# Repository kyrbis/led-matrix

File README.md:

# led-matrix
led matrix board
:)!!

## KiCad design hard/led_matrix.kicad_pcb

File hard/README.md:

# LED Matrix hardware
via KiCad (https://kicad.org/), tuned for order on JLCPCB (https://jlcpcb.com/).  
All capacitors X7R or better.

_PCB Preview_

## KiCad Readme
### Libraries (*.lib)
Additional fields/attributes as in following example:

| Name | Value |
| ----:|:----- |
| DigiKey | IRLML0030TRPBFCT-ND |
| Mouser | 942-IRLML0030TRPBF |
| LCSC | C67272 |
| MF | Infineon Technologies |
| MPN | IRLML0030TRPBF |
| Description | MOSFET N-CH 30V 5.3A SOT23 |

### Footprints (*.pretty)
_See https://kicad.org/libraries/klc/_

Use naming scheme `TYPE_MF_PART`  
Example: `LED_LiteOn_LTST-S270TBKT.kicad_mod`

### 3D (*.step)
Use same naming scheme as for footprints in dedicated 3D folder. In order to see 3D packages, setup `${LED_MATRIX_3D}` as path for your own folder.   
Example: `./3D/LED_LiteOn_LTST-S270TBKT.step`

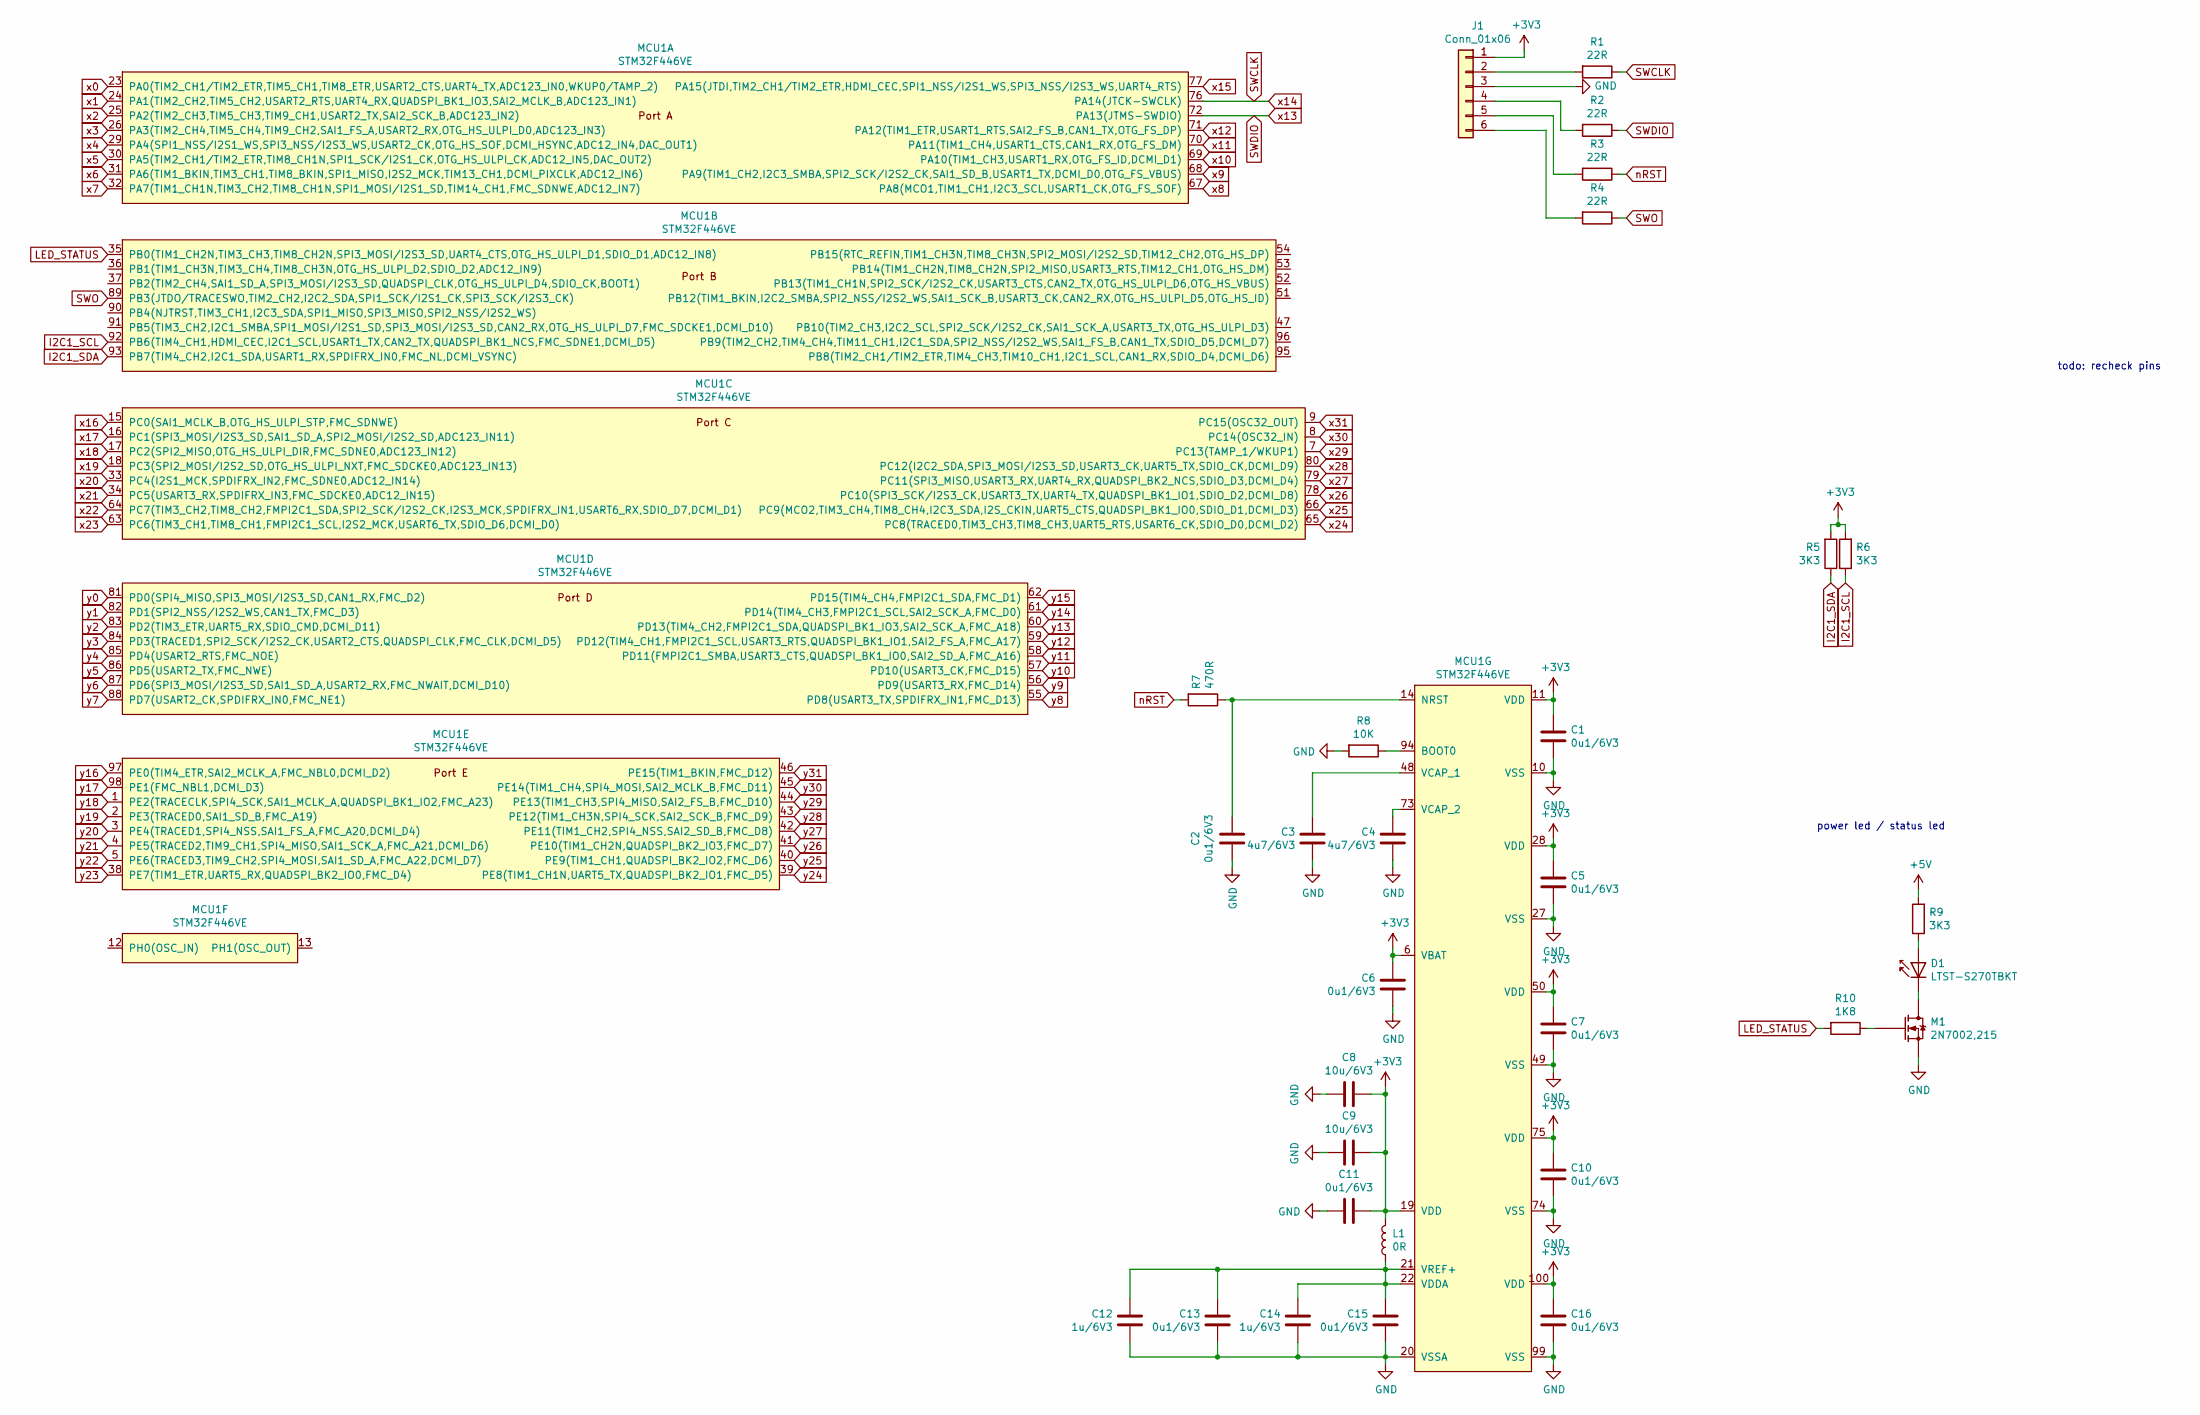
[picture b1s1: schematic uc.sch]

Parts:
C1, C2, C5, C6, C7, C10, C11, C13, C15, C16: 0u1/6V3; C_0402_1005Metric
C3, C4: 4u7/6V3; C_0805_2012Metric
C8, C9: 10u/6V3; C_0805_2012Metric
C12, C14: 1u/6V3; C_0805_2012Metric
D1: LTST-S270TBKT; LED_LiteOn_LTST-S270TBKT; Mouser_Part_Number 859-LTST-S270TBKT; DigiKey_Part_Number LTST-S270TBKT-5A-ND
J1: Conn_01x06; PinHeader_1x06_P2.54mm_Vertical
L1: 0R; R_1206_3216Metric
M1: 2N7002,215; SOT-23; MPN 2N7002,215; JLCPCB_Part_Number C65189
MCU1: STM32F446VE; MPN STM32F446VET6; JLCPCB_Part_Number C91929
R1, R2, R3, R4: 22R; R_0402_1005Metric
R5, R6, R9: 3K3; R_0402_1005Metric
R7: 470R; R_0402_1005Metric
R8: 10K; R_0402_1005Metric
R10: 1K8; R_0402_1005Metric

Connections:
+3V3: C1.1, C5.1, C6.2, C7.1, C8.2, C9.2, C10.1, C11.2, C16.1, J1.1, L1.1, MCU1.6 (VBAT), MCU1.11 (VDD), MCU1.19 (VDD), MCU1.28 (VDD), MCU1.50 (VDD), MCU1.75 (VDD), MCU1.100 (VDD), R5.2, R6.2; also elsewhere on the board
+5V: R9.2; also elsewhere on the board
GND: C1.2, C2.1, C3.1, C4.1, C5.2, C6.1, C7.2, C8.1, C9.1, C10.2, C11.1, C12.1, C13.1, C14.1, C15.1, C16.2, J1.3, M1.2 (S), MCU1.10 (VSS), MCU1.20 (VSSA), MCU1.27 (VSS), MCU1.49 (VSS), MCU1.74 (VSS), MCU1.99 (VSS), R8.2; also elsewhere on the board
I2C1_SCL: MCU1.92 (PB6(TIM4_CH1,HDMI_CEC,I2C1_SCL,USART1_T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), R6.1; also elsewhere on the board
I2C1_SDA: MCU1.93 (PB7(TIM4_CH2,I2C1_SDA,USART1_RX,SPDIFRX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), R5.1; also elsewhere on the board
LED_STATUS: MCU1.35 (PB0(TIM1_CH2N,TIM3_CH3,TIM8_CH2N,SPI3_M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), R10.2
unnamed: C2.2, MCU1.14 (NRST), R7.1
unnamed: C3.2, MCU1.48 (VCAP_1)
unnamed: C4.2, MCU1.73 (VCAP_2)
unnamed: C12.2, C13.2, C14.2, C15.2, L1.2, MCU1.21 (VREF+), MCU1.22 (VDDA)
unnamed: D1.A, R9.1
unnamed: D1.C, M1.3 (D)
unnamed: J1.2, R1.2
unnamed: J1.4, R2.2
unnamed: J1.5, R3.2
unnamed: J1.6, R4.2
unnamed: M1.1 (G), R10.1
unnamed: MCU1.94 (BOOT0), R8.1
SWCLK: MCU1.76 (PA14(JTCK-SWCLK)), R1.1; also elsewhere on the board
SWDIO: MCU1.72 (PA13(JTMS-SWDIO)), R2.1; also elsewhere on the board
SWO: MCU1.89 (PB3(JTDO/TRACESWO,TIM2_CH2,I2C2_SDA,SPI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), R4.1
nRST: R3.1, R7.2
x0: MCU1.23 (PA0(TIM2_CH1/TIM2_ETR,TIM5_CH1,TIM8_ETR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); also elsewhere on the board
x1: MCU1.24 (PA1(TIM2_CH2,TIM5_CH2,USART2_RTS,UART4_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); also elsewhere on the board
x2: MCU1.25 (PA2(TIM2_CH3,TIM5_CH3,TIM9_CH1,USART2_T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); also elsewhere on the board
x3: MCU1.26 (PA3(TIM2_CH4,TIM5_CH4,TIM9_CH2,SAI1_FS_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); also elsewhere on the board
x4: MCU1.29 (PA4(SPI1_NSS/I2S1_WS,SPI3_NSS/I2S3_WS,U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); also elsewhere on the board
x5: MCU1.30 (PA5(TIM2_CH1/TIM2_ETR,TIM8_CH1N,SPI1_SC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); also elsewhere on the board
x6: MCU1.31 (PA6(TIM1_BKIN,TIM3_CH1,TIM8_BKIN,SPI1_M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); also elsewhere on the board
x7: MCU1.32 (PA7(TIM1_CH1N,TIM3_CH2,TIM8_CH1N,SPI1_M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); also elsewhere on the board
x8: MCU1.67 (PA8(MCO1,TIM1_CH1,I2C3_SCL,USART1_CK,OT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); also elsewhere on the board
x9: MCU1.68 (PA9(TIM1_CH2,I2C3_SMBA,SPI2_SCK/I2S2_CK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); also elsewhere on the board
x10: MCU1.69 (PA10(TIM1_CH3,USART1_RX,OTG_FS_ID,DCMI_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); also elsewhere on the board
x11: MCU1.70 (PA11(TIM1_CH4,USART1_CTS,CAN1_RX,OTG_FS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); also elsewhere on the board
x12: MCU1.71 (PA12(TIM1_ETR,USART1_RTS,SAI2_FS_B,CAN1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); also elsewhere on the board
x15: MCU1.77 (PA15(JTDI,TIM2_CH1/TIM2_ETR,HDMI_CEC,SP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); also elsewhere on the board
x16: MCU1.15 (PC0(SAI1_MCLK_B,OTG_HS_ULPI_STP,FMC_SDN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); also elsewhere on the board
x17: MCU1.16 (PC1(SPI3_MOSI/I2S3_SD,SAI1_SD_A,SPI2_MO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); also elsewhere on the board
x18: MCU1.17 (PC2(SPI2_MISO,OTG_HS_ULPI_DIR,FMC_SDNE0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); also elsewhere on the board
x19: MCU1.18 (PC3(SPI2_MOSI/I2S2_SD,OTG_HS_ULPI_NXT,F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); also elsewhere on the board
x20: MCU1.33 (PC4(I2S1_MCK,SPDIFRX_IN2,FMC_SDNE0,ADC1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); also elsewhere on the board
x21: MCU1.34 (PC5(USART3_RX,SPDIFRX_IN3,FMC_SDCKE0,AD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); also elsewhere on the board
x22: MCU1.64 (PC7(TIM3_CH2,TIM8_CH2,FMPI2C1_SDA,SPI2_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); also elsewhere on the board
x23: MCU1.63 (PC6(TIM3_CH1,TIM8_CH1,FMPI2C1_SCL,I2S2_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); also elsewhere on the board
x24: MCU1.65 (PC8(TRACED0,TIM3_CH3,TIM8_CH3,UART5_RTS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); also elsewhere on the board
x25: MCU1.66 (PC9(MCO2,TIM3_CH4,TIM8_CH4,I2C3_SDA,I2S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); also elsewhere on the board
x26: MCU1.78 (PC10(SPI3_SCK/I2S3_CK,USART3_TX,UART4_T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); also elsewhere on the board
x27: MCU1.79 (PC11(SPI3_MISO,USART3_RX,UART4_RX,QUADS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); also elsewhere on the board
x28: MCU1.80 (PC12(I2C2_SDA,SPI3_MOSI/I2S3_SD,USART3_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); also elsewhere on the board
x29: MCU1.7 (PC13(TAMP_1/WKUP1)); also elsewhere on the board
x30: MCU1.8 (PC14(OSC32_IN)); also elsewhere on the board
x31: MCU1.9 (PC15(OSC32_OUT)); also elsewhere on the board
y0: MCU1.81 (PD0(SPI4_MISO,SPI3_MOSI/I2S3_SD,CAN1_RX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); also elsewhere on the board
y1: MCU1.82 (PD1(SPI2_NSS/I2S2_WS,CAN1_TX,FMC_D3)); also elsewhere on the board
y2: MCU1.83 (PD2(TIM3_ETR,UART5_RX,SDIO_CMD,DCMI_D11)); also elsewhere on the board
y3: MCU1.84 (PD3(TRACED1,SPI2_SCK/I2S2_CK,USART2_CTS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); also elsewhere on the board
y4: MCU1.85 (PD4(USART2_RTS,FMC_NOE)); also elsewhere on the board
y5: MCU1.86 (PD5(USART2_TX,FMC_NWE)); also elsewhere on the board
y6: MCU1.87 (PD6(SPI3_MOSI/I2S3_SD,SAI1_SD_A,USART2_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); also elsewhere on the board
y7: MCU1.88 (PD7(USART2_CK,SPDIFRX_IN0,FMC_NE1)); also elsewhere on the board
y8: MCU1.55 (PD8(USART3_TX,SPDIFRX_IN1,FMC_D13)); also elsewhere on the board
y9: MCU1.56 (PD9(USART3_RX,FMC_D14)); also elsewhere on the board
y10: MCU1.57 (PD10(USART3_CK,FMC_D15)); also elsewhere on the board
y11: MCU1.58 (PD11(FMPI2C1_SMBA,USART3_CTS,QUADSPI_BK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); also elsewhere on the board
y12: MCU1.59 (PD12(TIM4_CH1,FMPI2C1_SCL,USART3_RTS,QU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); also elsewhere on the board
y13: MCU1.60 (PD13(TIM4_CH2,FMPI2C1_SDA,QUADSPI_BK1_I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); also elsewhere on the board
y14: MCU1.61 (PD14(TIM4_CH3,FMPI2C1_SCL,SAI2_SCK_A,FM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); also elsewhere on the board
y15: MCU1.62 (PD15(TIM4_CH4,FMPI2C1_SDA,FMC_D1)); also elsewhere on the board
y16: MCU1.97 (PE0(TIM4_ETR,SAI2_MCLK_A,FMC_NBL0,DCMI_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); also elsewhere on the board
y17: MCU1.98 (PE1(FMC_NBL1,DCMI_D3)); also elsewhere on the board
y18: MCU1.1 (PE2(TRACECLK,SPI4_SCK,SAI1_MCLK_A,QUADS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); also elsewhere on the board
y19: MCU1.2 (PE3(TRACED0,SAI1_SD_B,FMC_A19)); also elsewhere on the board
y20: MCU1.3 (PE4(TRACED1,SPI4_NSS,SAI1_FS_A,FMC_A20,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); also elsewhere on the board
y21: MCU1.4 (PE5(TRACED2,TIM9_CH1,SPI4_MISO,SAI1_SCK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); also elsewhere on the board
y22: MCU1.5 (PE6(TRACED3,TIM9_CH2,SPI4_MOSI,SAI1_SD_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); also elsewhere on the board
y23: MCU1.38 (PE7(TIM1_ETR,UART5_RX,QUADSPI_BK2_IO0,F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); also elsewhere on the board
y24: MCU1.39 (PE8(TIM1_CH1N,UART5_TX,QUADSPI_BK2_IO1,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); also elsewhere on the board
y25: MCU1.40 (PE9(TIM1_CH1,QUADSPI_BK2_IO2,FMC_D6)); also elsewhere on the board
y26: MCU1.41 (PE10(TIM1_CH2N,QUADSPI_BK2_IO3,FMC_D7)); also elsewhere on the board
y27: MCU1.42 (PE11(TIM1_CH2,SPI4_NSS,SAI2_SD_B,FMC_D8)); also elsewhere on the board
y28: MCU1.43 (PE12(TIM1_CH3N,SPI4_SCK,SAI2_SCK_B,FMC_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); also elsewhere on the board
y29: MCU1.44 (PE13(TIM1_CH3,SPI4_MISO,SAI2_FS_B,FMC_D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); also elsewhere on the board
y30: MCU1.45 (PE14(TIM1_CH4,SPI4_MOSI,SAI2_MCLK_B,FMC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); also elsewhere on the board
y31: MCU1.46 (PE15(TIM1_BKIN,FMC_D12)); also elsewhere on the board

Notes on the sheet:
power led / status led
todo: recheck pins
